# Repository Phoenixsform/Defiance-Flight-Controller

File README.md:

# Defiance-Flight-Controller
An ESP32-S3 based universal flight controller. Not really mean for me to use, but for future students and other teams.

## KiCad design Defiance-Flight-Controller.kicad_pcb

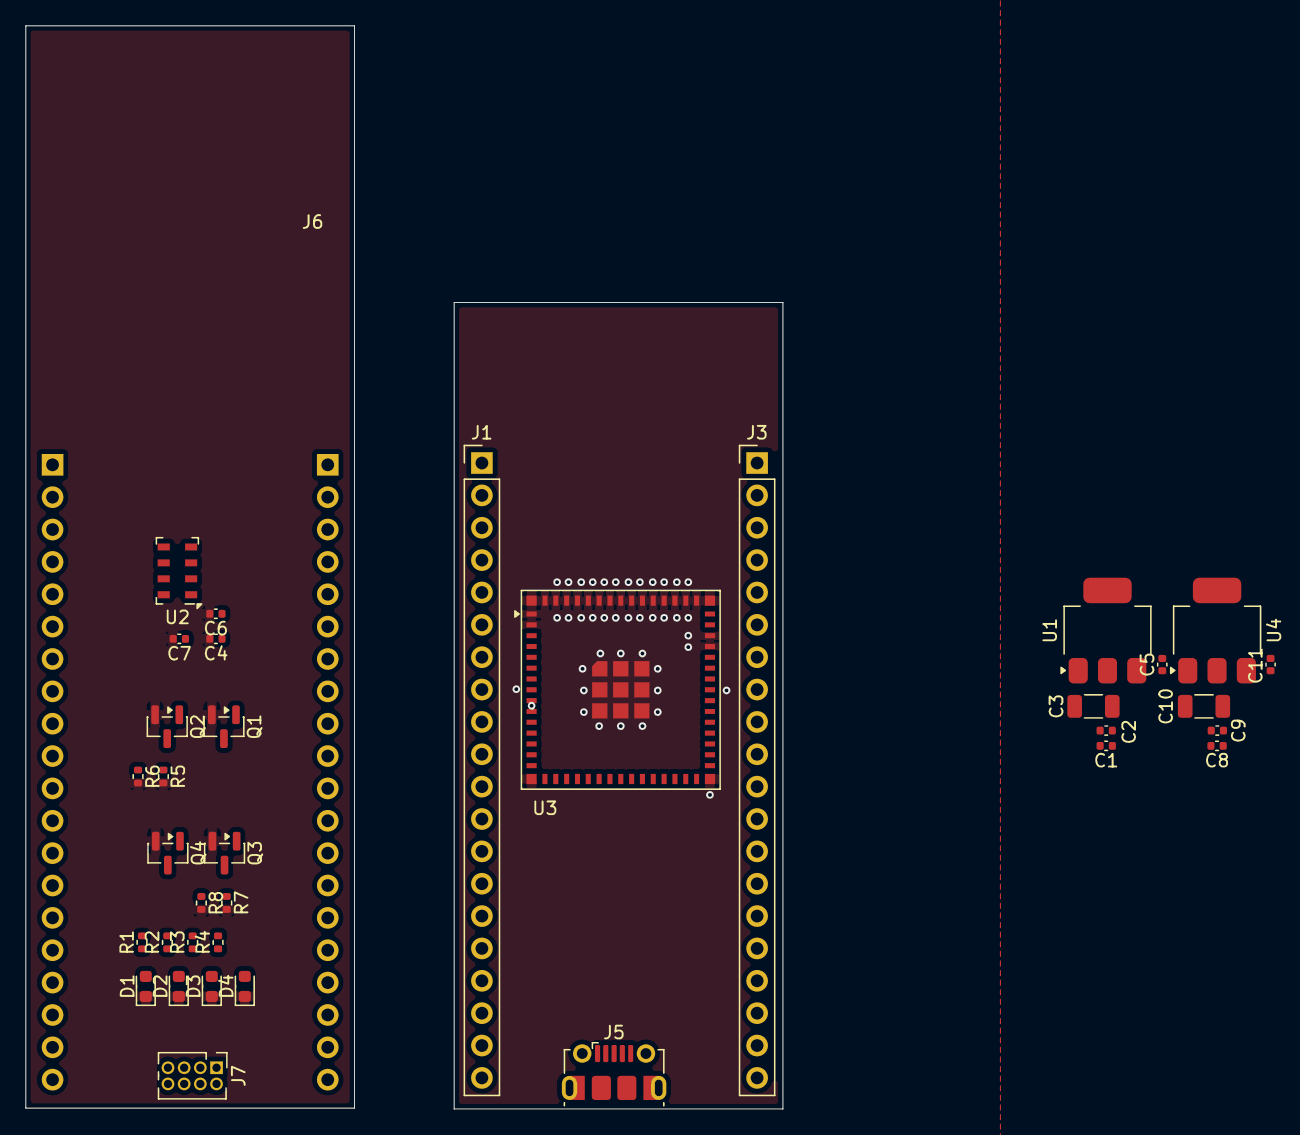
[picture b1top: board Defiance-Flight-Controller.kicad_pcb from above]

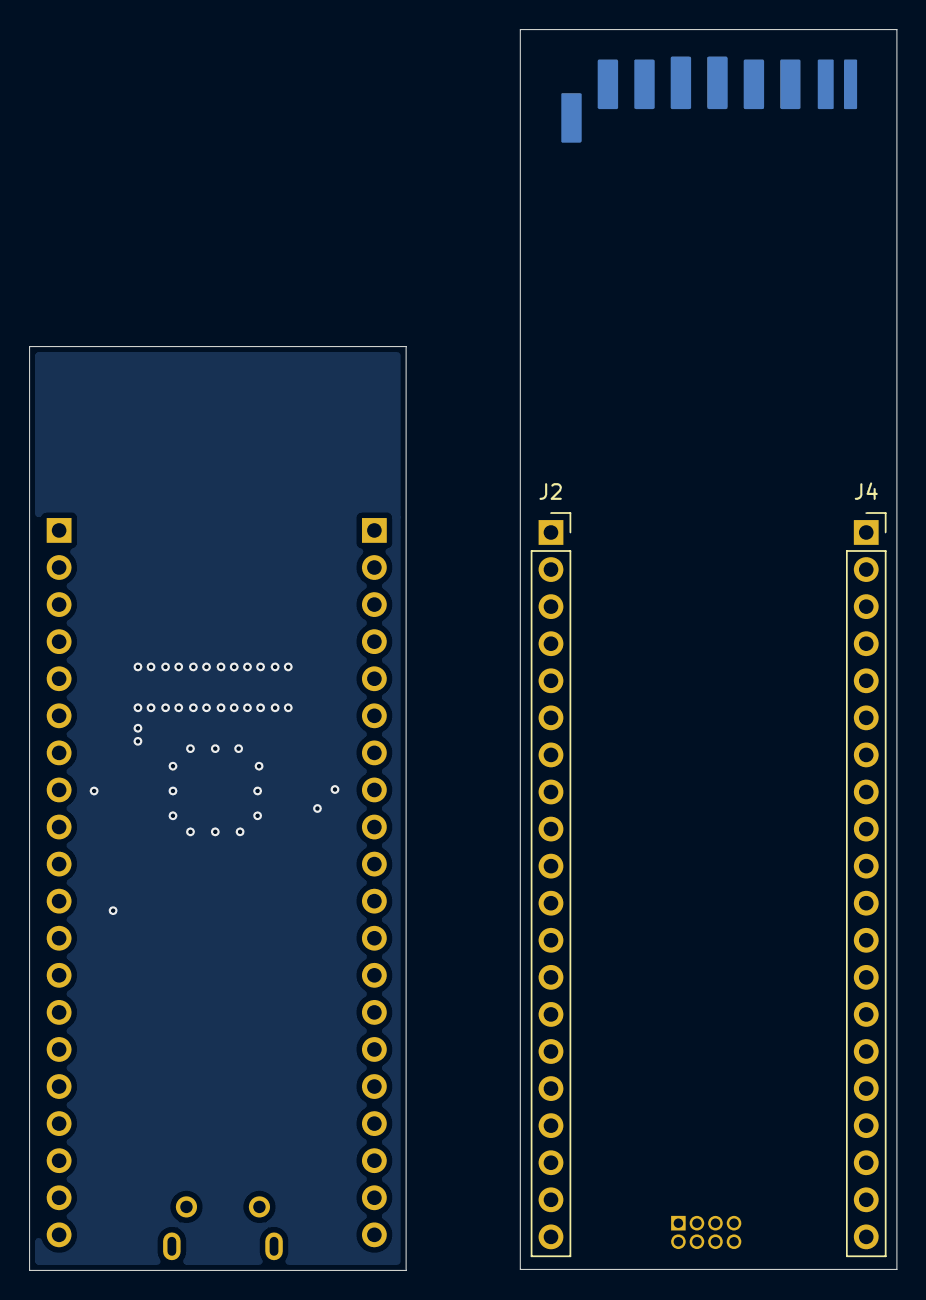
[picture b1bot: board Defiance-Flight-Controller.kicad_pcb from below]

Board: 2 copper layers, 59.4 x 85.0 mm, 38 parts (2 on the bottom side), 19 nets, no tracks yet.

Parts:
C1, C2, C4, C5, C6, C7, C8, C9, C11: 100nF; C_0402_1005Metric
C3, C10: 10uF; C_1206_3216Metric
D1, D2, D3, D4: D; D_0603_1608Metric
J1, J3: Conn_01x20_Pin; PinHeader_1x20_P2.54mm_Vertical
J2, J4: Conn_01x20_Socket; PinSocket_1x20_P2.54mm_Vertical
J5: USB_OTG; USB_Micro-B_Molex-105017-0001
J6: SD_Card_Device; SD_Card_Device_16mm_SlotDepth
J7: Conn_01x08; PinHeader_2x04_P1.27mm_Vertical
Q1, Q2, Q3, Q4: AO3400A; SOT-23
R1, R2, R3, R4, R5, R6, R7, R8: R; R_0402_1005Metric
U1: AMS1117-5.0; SOT-223-3_TabPin2
U2: MS5611-01BA; LGA-8_3x5mm_P1.25mm
U3: ESP32-S3-MINI-1U; ESP32-S2-MINI-1U
U4: AMS1117-3.3; SOT-223-3_TabPin2

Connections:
+3.3V: C4.1, C6.1, C7.1, C8.1, C9.1, C10.1, U4.2 (VO)
+5V: C1.1, C2.1, C3.1, U1.2 (VO)
GND: C1.2, C2.2, C3.2, C4.2, C5.2, C6.2, C7.2, C8.2, C9.2, C10.2, C11.2, D1.1 (K), D2.1 (K), D3.1 (K), D4.1 (K), Q1.2 (S), Q2.2 (S), Q3.2 (S), Q4.2 (S), R5.2, R6.2, R7.2, R8.2, U1.1 (GND), U3.1 (GND), U3.2 (GND), U3.42 (GND), U3.43 (GND), U3.46 (GND), U3.47 (GND), U3.48 (GND), U3.49 (GND), U3.50 (GND), U3.51 (GND), U3.52 (GND), U3.53 (GND), U3.54 (GND), U3.55 (GND), U3.56 (GND), U3.57 (GND), U3.58 (GND), U3.59 (GND), U3.60 (GND), U3.61 (GND), U3.62 (GND), U3.63 (GND), U3.64 (GND), U3.65 (GND), U4.1 (GND)
unnamed: D1.2 (A), R1.2
unnamed: D2.2 (A), R2.2
unnamed: D3.2 (A), R3.2
unnamed: D4.2 (A), R4.2
unnamed: J6.3 (VSS), J6.6 (VSS)
unnamed: J7.2, Q1.3 (D)
unnamed: J7.4, Q2.3 (D)
unnamed: J7.6, Q3.3 (D)
unnamed: J7.8, Q4.3 (D)
unnamed: Q1.1 (G), R5.1
unnamed: Q2.1 (G), R6.1
unnamed: Q3.1 (G), R7.1
unnamed: Q4.1 (G), R8.1
unnamed: U2.4 (CSB), U2.5 (CSB)
VBUS: J7.1, J7.3, J7.5, J7.7
VIN: C5.1, C11.1, U1.3 (VI), U4.3 (VI)
